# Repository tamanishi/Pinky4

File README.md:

# Pinky4

> **Warning**  
> If you are using Kicad 6, please see https://github.com/tamanishi/Pinky4/issues/4 .

A split 4 x 7 vertically staggered keys and 4 thumb keys keyboard.  
An idea is inspired from [crkbd](https://github.com/foostan/crkbd), [Lily58](https://github.com/kata0510/Lily58), [Ergo42](https://github.com/Biacco42/Ergo42) and [Helix](https://github.com/MakotoKurauchi/helix).  
Pinky4 is designed for PoC.

# Pcb & Plates

# Bill of Materials (for both hands)
| # | name | qty |
| ---: | :--- | ---: |
| 1 | pcbs | 2 |
| 2 | top plates | 2 |
| 3 | bottom plates | 2 |
| 4 | Pro Micros | 2 |
| 5 | 2 pins tact switches | 2 |
| 6 | TRRS connectors | 2 |
| 7 | diodes (1N4148 or 1N4148W) | 64 |
| 8 | Kailh PCB Sockets (MX Sockets) | 56 |
| 9 | Kailh PCB Sockets (Choc Sockets) | 8 |
| 10 | Cherry MX compatible keyswitches | 56 |
| 11 | Kailh low profile (Choc) keyswitches | 8 |
| 12 | Cherry MX compatible keycaps | 56 |
| 13 | Kailh low profile (Choc) compatible keycaps | 8 |
| 14 | TRS or TRRS cable | 1 |
| 15 | 7mm M2 standoffs (for top and bottom plates) | 12 |
| 16 | 5mm M2 standoffs (for Pro Micro cover plates) | 4 |
| 17 | 4mm M2 screws | 32 |
| 18 | rubber cushions | 8 |

# Notes

# Firmware
See [Quantum Mechanical Keyboard Firmware](https://qmk.fm) and [its Pinky support page](https://github.com/qmk/qmk_firmware/blob/master/keyboards/pinky/readme.md)

## TODOs
- [x] add images
- [x] add BOM
- [ ] add build log

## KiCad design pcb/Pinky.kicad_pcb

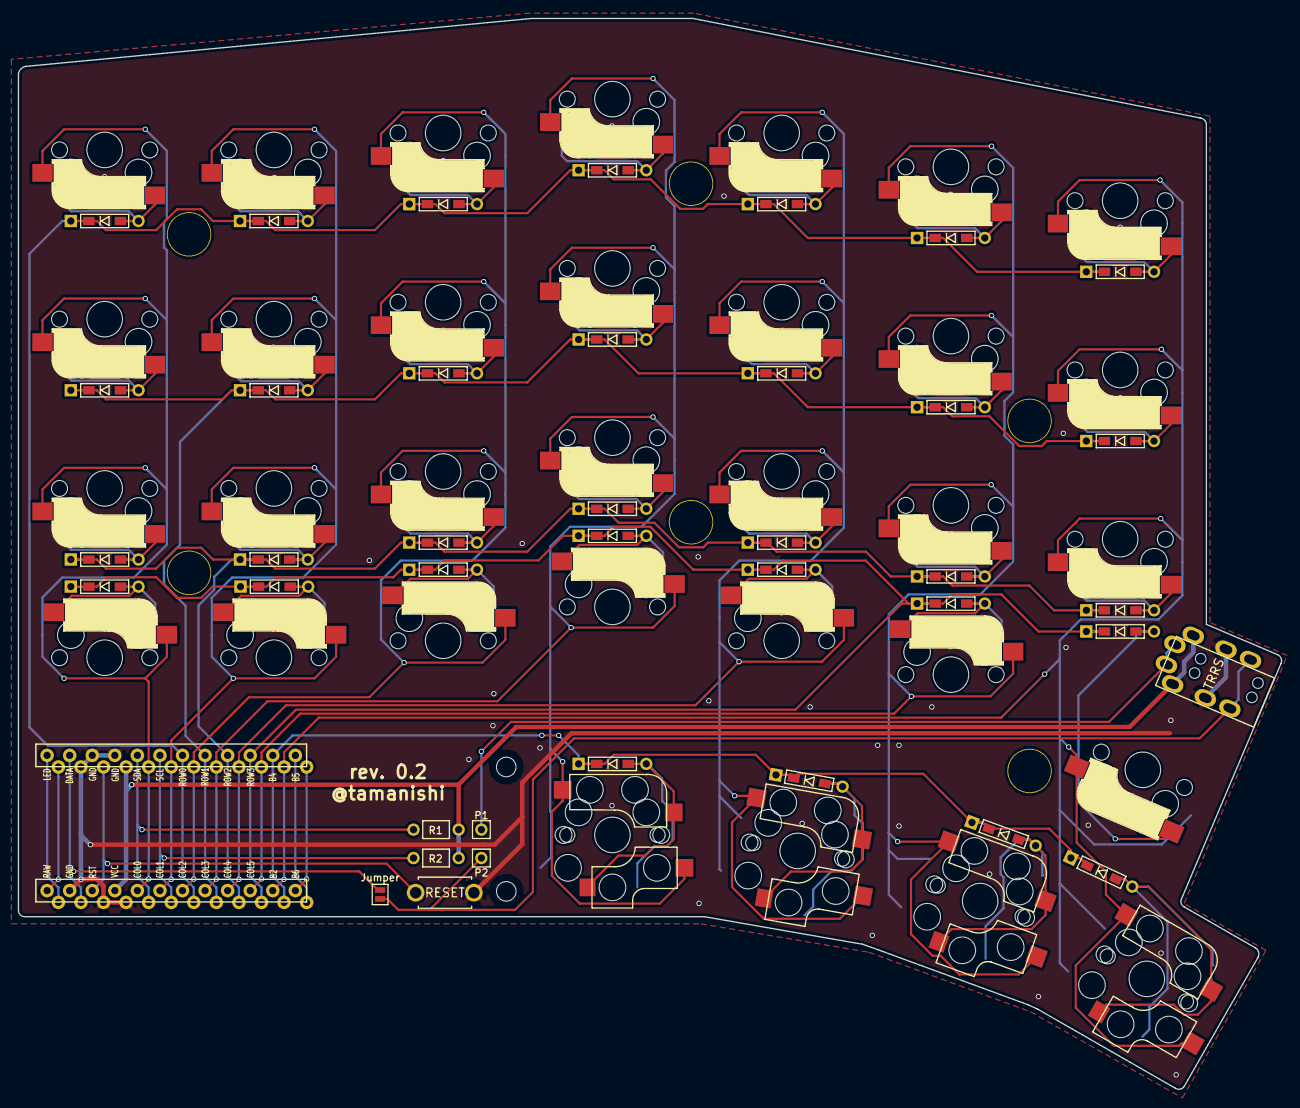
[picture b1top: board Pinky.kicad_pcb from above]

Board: 2 copper layers, 142.2 x 120.5 mm, 80 parts (0 on the bottom side), 52 nets.

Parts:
D1, D2, D3, D4, D5, D6, D7, D8, D9, D10, D11, D12, D13, D14, D15, D16, D17, D18, D19, D20, D21, D22, D23, D24, D25, D26, D27, D28, D29, D30, D31, D32: D; D3_TH_SMD
HOLE_M2, HOLE_M2#2: VAL**; HOLE_M2
J1: MJ-4PP-9
JP1: Jumper
P1, P2: i2c-pin; 1pin_conn
R1, R2: R
Ref**: Val**; HOLE
Ref**#2, Ref**#3, Ref**#4, Ref**#5, Ref**#6: Val**; HOLE
SW1: RESET_SW; ResetSW
SW2, SW3, SW4, SW5, SW6, SW7, SW8, SW9, SW10, SW11, SW12, SW13, SW14, SW15, SW16, SW17, SW19, SW20, SW21, SW22, SW24, SW25, SW26, SW27, SW29, SW30, SW31, SW32: SW_PUSH; CherryMX_Hotswap
SW18, SW23, SW28, SW33: SW_PUSH; CherryMX_KailhLowProfile_Hotswap
U1: ProMicro; ProMicro_v2

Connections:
GND: J1.C, SW1.2, U1.3, U1.4, U1.23
unnamed: D1.2, SW2.2
unnamed: D2.2, SW3.2
unnamed: D3.2, SW4.2
unnamed: D4.2, SW5.2
unnamed: D5.2, SW6.2
unnamed: D6.2, SW7.2
unnamed: D7.2, SW8.2
unnamed: D8.2, SW9.2
unnamed: D9.2, SW10.2
unnamed: D10.2, SW11.2
unnamed: D11.2, SW12.2
unnamed: D12.2, SW13.2
unnamed: D13.2, SW14.2
unnamed: D14.2, SW15.2
unnamed: D15.2, SW16.2
unnamed: D16.2, SW17.2
unnamed: D17.2, SW18.2
unnamed: D18.2, SW19.2
unnamed: D19.2, SW20.2
unnamed: D20.2, SW21.2
unnamed: D21.2, SW22.2
unnamed: D22.2, SW23.2
unnamed: D23.2, SW24.2
unnamed: D24.2, SW25.2
unnamed: D25.2, SW26.2
unnamed: D26.2, SW27.2
unnamed: D27.2, SW28.2
unnamed: D28.2, SW29.2
unnamed: D29.2, SW30.2
unnamed: D30.2, SW31.2
unnamed: D31.2, SW32.2
unnamed: D32.2, SW33.2
unnamed: J1.A, P1.1
unnamed: J1.B, JP1.1, P2.1
VCC: J1.D, R1.1, R2.1, U1.21
col0: SW2.1, SW3.1, SW4.1, SW5.1, U1.20
col1: SW6.1, SW7.1, SW8.1, SW9.1, U1.19
col2: SW10.1, SW11.1, SW12.1, SW13.1, U1.18
col3: SW14.1, SW15.1, SW16.1, SW17.1, SW18.1, U1.17
col4: SW19.1, SW20.1, SW21.1, SW22.1, SW23.1, U1.16
col5: SW24.1, SW25.1, SW26.1, SW27.1, SW28.1, U1.15
col6: SW29.1, SW30.1, SW31.1, SW32.1, SW33.1, U1.14
data: JP1.2, U1.2
reset: SW1.1, U1.22
row0: D1.1, D5.1, D9.1, D13.1, D18.1, D23.1, D28.1, U1.7
row1: D2.1, D6.1, D10.1, D14.1, D19.1, D24.1, D29.1, U1.8
row2: D3.1, D7.1, D11.1, D15.1, D20.1, D25.1, D30.1, U1.9
row3: D4.1, D8.1, D12.1, D16.1, D21.1, D26.1, D31.1, U1.10
row4: D17.1, D22.1, D27.1, D32.1, U1.11
scl: R2.2, U1.6
sda: R1.2, U1.5

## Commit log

2018-11-04 add LICENSE
2018-11-04 [WIP] wiring & layouting
2018-11-08 [WIP] layout completed
2018-11-11 [WIP] wiring
2018-11-18 finished wiring
2018-11-18 add top plate layer
2018-11-18 tweaked wiring
2018-11-23 change direction of some keyswitches and tweak wiring
2018-11-25 sent to allpcb
2018-11-26 0.1mm の精度の設定を全て消したつもり。
2018-11-27 confirm 0.1mm hole size
2018-12-02 remove 0.1mm holes
2018-12-03 add HOLE_M2 for promicro cover
2018-12-06 move promicro outside
2018-12-09 move thumb keys inside
2018-12-10 add plates
2018-12-11 first edit
2018-12-11 capitalized
2018-12-11 add to gitignore plate gerber files
2018-12-28 - readme - rename to Pinky4
2019-01-18 - add image - maintain README.md
2019-01-19 move trrs layout tweaking to another branch
2019-01-19 add pcb image
2019-01-19 tweak trrs layout
2019-01-19 add pcb plates images
2019-01-19 add notes
2019-01-19 update note about jumper soldering.
2019-11-27 maintain logo svg file
2020-02-24 jumper
2020-03-08 add planck keycap picture
2020-05-25 add image
2020-06-13 improve the note.
